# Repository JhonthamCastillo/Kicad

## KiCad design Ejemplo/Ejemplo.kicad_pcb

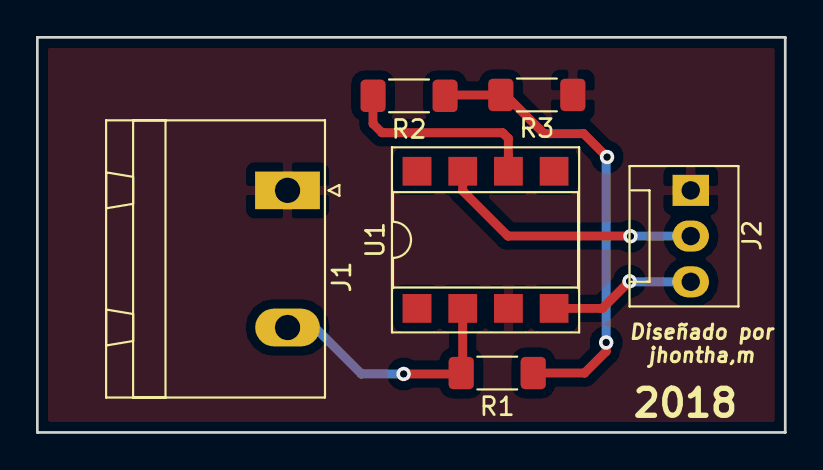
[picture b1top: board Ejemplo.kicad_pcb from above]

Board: 2 copper layers, 41.6 x 21.9 mm, 6 parts (0 on the bottom side), 6 nets.

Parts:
J1: Conn_01x02_Female; PhoenixContact_GMSTBA_2,5_2-G-7,62_1x02_P7.62mm_Horizontal
J2: Conn_01x03_Female; FanPinHeader_1x03_P2.54mm_Vertical
R1: 2k; R_1806_4516Metric
R2: 100; R_1806_4516Metric
R3: 1k; R_1806_4516Metric
U1: LM741; DIP-8_W7.62mm_SMDSocket_SmallPads

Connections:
+12V: J2.2, U1.7
-12V: J2.3, U1.4
GND: J1.1, J2.1, R3.1, U1.3
unnamed: J1.2, R1.2, U1.2
unnamed: R1.1, R2.1, R3.2
unnamed: R2.2, U1.6

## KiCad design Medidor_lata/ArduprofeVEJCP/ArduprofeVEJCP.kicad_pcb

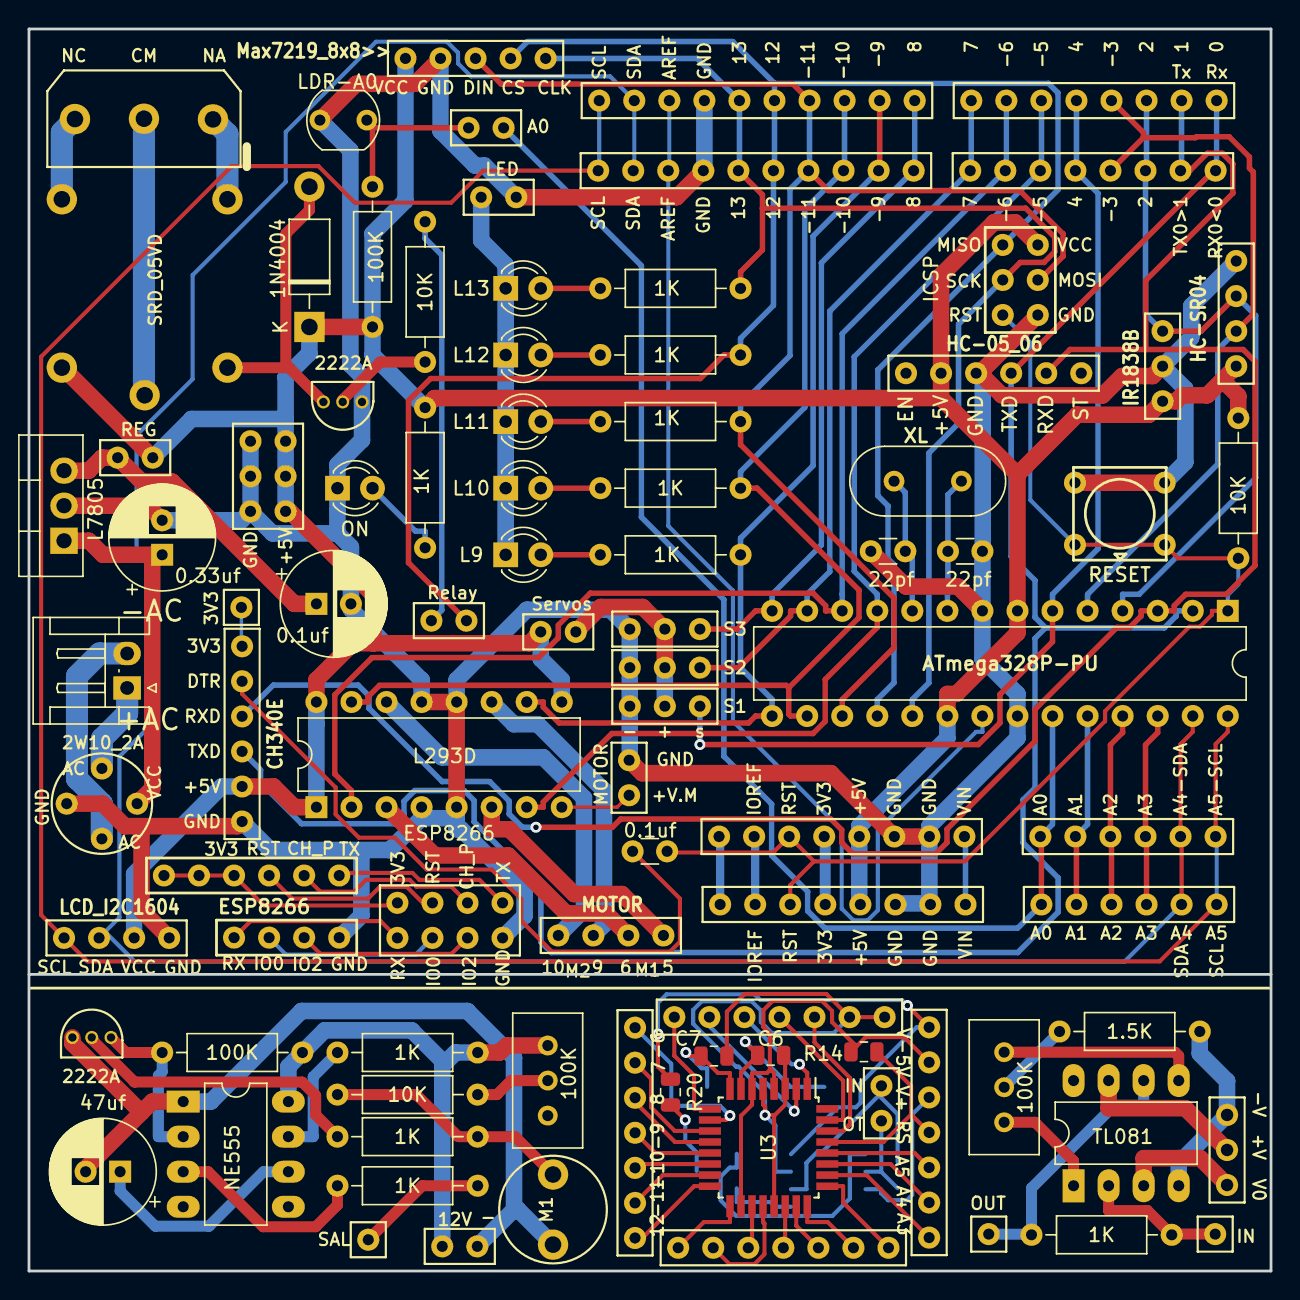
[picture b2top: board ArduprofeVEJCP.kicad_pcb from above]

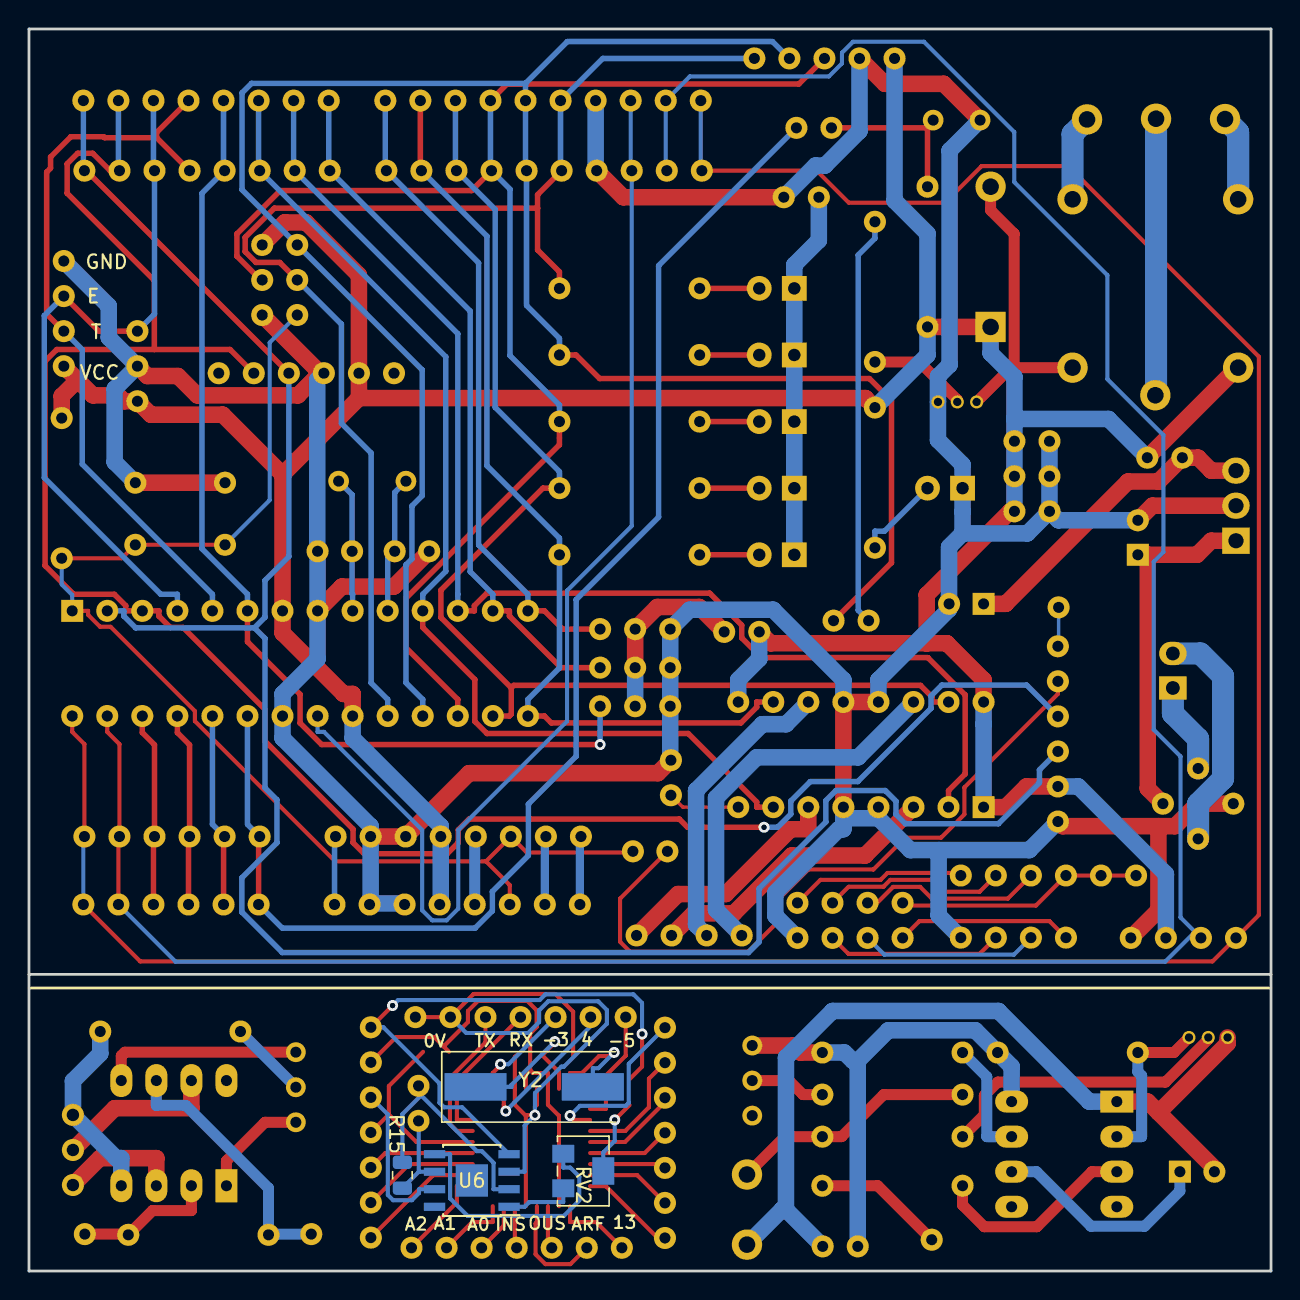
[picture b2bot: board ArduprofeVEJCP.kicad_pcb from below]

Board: 2 copper layers, 90.0 x 90.0 mm, 88 parts (4 on the bottom side), 115 nets.

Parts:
C1: 0.33uf; CP_Radial_D7.5mm_P2.50mm
C2: 0.1uf; CP_Radial_D7.5mm_P2.50mm
C3, C4: 22pf; C_Disc_D3.0mm_W1.6mm_P2.50mm
C5: 0.1uf; C_Disc_D3.0mm_W1.6mm_P2.50mm
C6, C7: 22p; C_0805_2012Metric
C8: 47uf; CP_Radial_D7.5mm_P2.50mm
CON1: SheldArduino; arduino_sheld
CONN1: ICSP
CONN2: S1; arduino_pin_servo
CONN3: S2; arduino_pin_servo
CONN4: ArduinoSheldExt; arduino_sheld_ext
CONN5: S3; arduino_pin_servo
CONN6: ESP8266; SocketESP8266
CONN7: Bornera_5.0_3P
CONN8: Max7219_8x8>>; Max7219_8x8
CONN9: MOTOR; L293D
D1: 1N4004; D_DO-41_SOD81_P10.16mm_Horizontal
D2: ON; LED_D3.0mm
D3: L9; LED_D3.0mm
D4: L10; LED_D3.0mm
D5: L11; LED_D3.0mm
D6: L12; LED_D3.0mm
D7: L13; LED_D3.0mm
J1: Conn_01x02_Female; POWER
J2: 3V3; arduino_pin_socket_1
J3: Conn_01x02_Female; JST_EH_S02B-EH_1x02_P2.50mm_Horizontal
J4: 12V; arduino_pin_socket_2
J5: IN; arduino_pin_socket_1
J6: OUT; arduino_pin_socket_1
J7: SAL; arduino_pin_socket_1
J8: Conn_01x03_Female; arduino_pin_socket_3
J9: ANALOG; arduino_pin_socket_7
J10, J11: DIGITAL; arduino_pin_socket_7
J12: Alimentacion; arduino_pin_socket_7
J13: Conn_01x02_Female; arduino_pin_socket_2
JP1: Relay; Jum2.54mm
JP2: A0; Jum2.54mm
JP3: MOTOR; Jum2.54mm
JP4: Servos; Jum2.54mm
JP5: LED; Jum2.54mm
JP6: REG; Jum2.54mm
LCD1: LCD_I2C1604; LCD_I2C_1604
M1: MIC
MOD1: ESP8266; WIFI_ESP8266
MOD2: HC-SR04
MOD3: HC-05_06
MOD4: CH340E; arduino_usb_ttl
Q1, Q2: 2222A; TRANSISTOR_TO_92ME
R1, R2, R11: 10K; R_Axial_DIN0207_L6.3mm_D2.5mm_P10.16mm_Horizontal
R3, R13: 100K; R_Axial_DIN0207_L6.3mm_D2.5mm_P10.16mm_Horizontal
R4, R6, R7, R8, R9, R10, R12, R16, R18, R19: 1K; R_Axial_DIN0207_L6.3mm_D2.5mm_P10.16mm_Horizontal
R5: LDR-A0; R_LDR_5.1x4.3mm_P3.4mm_Vertical
R14, R15: 1K; R_0805_2012Metric
R17: 1.5K; R_Axial_DIN0207_L6.3mm_D2.5mm_P10.16mm_Horizontal
R20: 1.5K; R_0805_2012Metric
RV1, RV3: 100K; Potentiometer_Bourns_3296W_Vertical
RV2: R_POT; Potentiometer_Bourns_3224W_Vertical
Relay1: SRD_05VD; SRD_05VDC_SL_C_5_V_DC_10A
SEN1: IR1838B; VS1838B
Sw1: RESET; Pulsador
U1: ATmega328P-PU; DIP-28_W7.62mm
U2: L7805; TO-220-3_Vertical
U3: ATmega328-AU; TQFP-32_7x7mm_P0.8mm
U4: L293D; DIP-16_W7.62mm
U5: 2W10_2A; 2W005_thru_2W10
U6: TL081; SOIC-8-1EP_3.9x4.9mm_P1.27mm_EP2.35x2.35mm
U7: NE555; DIP-8_W7.62mm_LongPads
U8: TL081; DIP-8_W7.62mm_LongPads
Y1: XL; Crystal_HC49-U_Vertical
Y2: XL; Crystal_SMD_HC49-SD

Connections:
3V3: CONN6.4, MOD1.4
4: J12.2, U3.2
7: J11.2, U3.11
8: J11.3, U3.12
12: J11.7, U3.16
13: J10.1, U3.17
+3V3: CON1.4, CONN4.4
+5V: CON1.5, CONN1.2, CONN4.5, CONN8.5, D1.1, J1.1, JP4.1, JP6.2, LCD1.2, MOD2.4, MOD3.2, MOD4.2, R2.2, R3.2, R4.1, Relay1.3, SEN1.3, U1.7, U1.20, U4.1, U4.9, U4.16
+30V: J3.1, U5.1
+S: CONN2.2, CONN3.2, CONN5.2, JP4.2
-3: J12.3, U3.1
-5: J12.1, U3.9
-6: J11.1, U3.10
-9: J11.4, U3.13
-10: J11.5, U3.14
-11: J11.6, U3.15
-30V: J3.2, U5.3
/C3: C3.2, U1.9, Y1.1
/C4: C4.1, U1.10, Y1.2
/C8: C8.1, U7.6
/INA: J5.1, R16.1, U8.2
/J412V: J4.2, R13.1, R18.2, RV1.3, U7.8
/L9: D3.2, R6.1
/L10: D4.2, R7.1
/L11: D5.2, R8.1
/L12: D6.2, R9.1
/L13: D7.2, R10.1
/LDR: JP2.1, R3.1, R5.2
/LED: D3.1, D4.1, D5.1, D6.1, D7.1, JP5.1
/LON: D2.2, R4.2
/M15: CONN9.1, U4.6
/M16: CONN9.2, U4.3
/M29: CONN9.3, U4.11
/M210: CONN9.4, U4.14
/M+: M1.2, R11.1, R12.2
/Micro328U/PV: R20.1, RV2.2
/OF1: RV3.3, U8.1
/OF2: RV3.1, U8.5
/OUTA: J6.1, R16.2, U8.6
/Q2B: Q2.2, R12.1
/Q2E: Q2.3, R13.2, U7.2
/QB: Q1.2, R1.1
/QE: D1.2, Q1.3, Relay1.1
/R18: R18.1, U7.7
/RL: JP1.1, R1.2
/RNA: CONN7.1, Relay1.5
/RNC: CONN7.3, Relay1.4
/RPT: R17.1, RV3.2
/RV1: R11.2, RV1.2
/SAL: J7.1, R19.1
/SSAL: R19.2, U7.3
AD6: J10.3, U3.19
AD7: J10.4, U3.22
AIN0: CON1.9, CONN4.9, JP2.2, U1.23
AIN1: CON1.10, CONN4.10, U1.24
AIN2: CON1.11, CONN4.11, U1.25
AIN3: CON1.12, CONN4.12, U1.26
AN0: J10.5, U3.23
AN1: J10.6, U3.24
AN2: J10.7, U3.25
AN3: J9.7, U3.26
AN4: J9.6, U3.27
AN5: J9.5, U3.28
AREF: CON1.30, CONN4.30, U1.21
ARF: J10.2, U3.20
C: CONN7.2, Relay1.2
CH: CONN6.2, MOD1.2
D2: CON1.17, CONN4.17, MOD2.2, SEN1.1, U1.4
D4: CON1.19, CONN2.3, CONN4.19, U1.6
D7: CON1.22, CONN3.3, CONN4.22, U1.13
D8: CON1.23, CONN4.23, CONN5.3, U1.14
D12: CON1.27, CONN1.1, CONN4.27, CONN8.2, JP1.2, R9.2, U1.18
D13: CON1.28, CONN1.3, CONN4.28, CONN8.1, R10.2, U1.19
DT: C5.1, MOD4.5
GND: C1.2, C2.2, C3.1, C4.2, CON1.6, CON1.7, CON1.29, CONN1.6, CONN2.1, CONN3.1, CONN4.6, CONN4.7, CONN4.29, CONN5.1, CONN6.8, CONN8.4, D2.1, J1.2, JP3.2, JP5.2, LCD1.1, MOD1.8, MOD2.1, MOD3.3, MOD4.1, Q1.1, R5.1, SEN1.2, Sw1.2, U1.8, U1.22, U2.2, U4.4, U4.5, U4.12, U4.13, U5.4
GND1: J8.1, U8.3
GND2: C8.2, J4.1, M1.1, Q2.1, U7.1
GND3: C6.1, C7.1, J12.6, J12.7, U3.3, U3.5, U3.21, U6.3
INS: J13.2, R15.2, U6.2
IO0: CONN6.6, MOD1.6
IO2: CONN6.7, MOD1.7
IOREF: CON1.2, CONN4.2
NC: CON1.1, CONN4.1
unnamed: J2.1, MOD4.6
unnamed: JP3.1, U4.8
OF1: RV2.3, U6.1
OF2: RV2.1, U6.5
OUTS: J13.1, R15.1, U6.6
PR: C1.1, U2.1, U5.2
PWM3: CON1.18, CONN4.18, MOD2.3, U1.5
PWM5: CON1.20, CONN4.20, U1.11, U4.7
PWM6: CON1.21, CONN4.21, U1.12, U4.2
PWM9: CON1.24, CONN4.24, R6.2, U1.15, U4.10
PWM10: CON1.25, CONN4.25, R7.2, U1.16, U4.15
PWM11: CON1.26, CONN1.4, CONN4.26, CONN8.3, R8.2, U1.17
RS: CONN6.3, MOD1.3
RS1: J9.4, R14.2, U3.29
RST: C5.2, CON1.3, CONN1.5, CONN4.3, R2.1, Sw1.1, U1.1
RX: CON1.15, CONN4.15, MOD3.4, MOD4.3, U1.2
RX1: CONN6.5, MOD1.5
RX2: J12.4, U3.31
Reg: C2.1, JP6.1, U2.3
SCL: CON1.14, CON1.32, CONN4.14, CONN4.32, LCD1.4, U1.28
SDA: CON1.13, CON1.31, CONN4.13, CONN4.31, LCD1.3, U1.27
TX: CON1.16, CONN4.16, MOD3.5, MOD4.4, U1.3
TX1: CONN6.1, MOD1.1
TX2: J12.5, U3.30
V+: J9.3, U6.7
V-: J9.1, R20.2, U6.4
VC+: J9.2, R14.1, U3.4, U3.6, U3.18
VCC+: J8.2, U8.7
VCC-: J8.3, R17.2, U8.4
VIN: CON1.8, CONN4.8
XT1: C6.2, U3.7, Y2.1
XT2: C7.2, U3.8, Y2.2

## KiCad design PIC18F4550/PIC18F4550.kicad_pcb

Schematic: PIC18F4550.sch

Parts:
D1, D2, D3, D4, D5, D6, D7, D8: LED; LED_0402_1005Metric
R1, R2, R3, R4, R5, R6, R7, R8: R; R_0603_1608Metric
U1: PIC18F4550-IP; DIP-40_W15.24mm

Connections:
+5V: U1.11 (VDD), U1.32 (VDD)
GND: R1.2, R2.2, R3.2, R4.2, R5.2, R6.2, R7.2, R8.2, U1.12 (VSS), U1.31 (VSS)
unnamed: D1.1, R1.1
unnamed: D1.2, U1.33 (RB0/AN12/INT0/FLT0/SDI/SDA)
unnamed: D2.1, R2.1
unnamed: D2.2, U1.34 (RB1/AN10/INT1/SCK/SCL)
unnamed: D3.1, R3.1
unnamed: D3.2, U1.35 (RB2/AN8/INT2/VMO)
unnamed: D4.1, R4.1
unnamed: D4.2, U1.36 (RB3/AN9/CCP2/VPO)
unnamed: D5.1, R5.1
unnamed: D5.2, U1.37 (RB4/AN11/KBI0/CSSPP)
unnamed: D6.1, R6.1
unnamed: D6.2, U1.38 (RB5/KBI1/PGM)
unnamed: D7.1, R7.1
unnamed: D7.2, U1.39 (RB6/KBI2/PGC)
unnamed: D8.1, R8.1
unnamed: D8.2, U1.40 (RB7/KBI3/PGD)

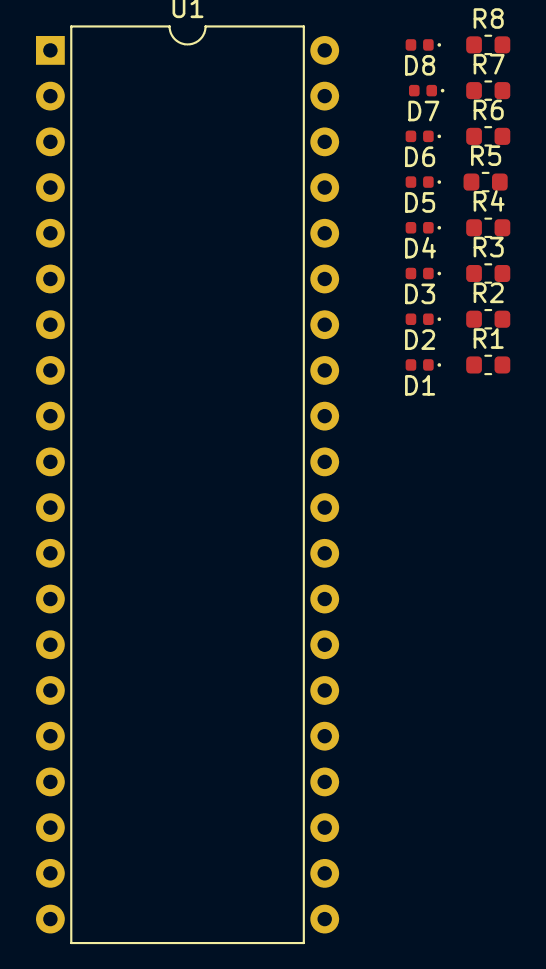
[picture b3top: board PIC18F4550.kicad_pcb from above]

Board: 2 copper layers, 17 parts (0 on the bottom side), 18 nets, no tracks yet.

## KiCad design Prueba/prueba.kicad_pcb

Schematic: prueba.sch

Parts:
C1, C2: C; C_Disc_D3.4mm_W2.1mm_P2.50mm
R1, R2: R; R_Axial_DIN0204_L3.6mm_D1.6mm_P5.08mm_Horizontal
U1: LM555; DIP-8_W7.62mm

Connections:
GND: C1.2, C2.2, U1.1 (GND)
unnamed: C1.1, U1.5 (CV)
unnamed: C2.1, R2.2, U1.2 (TR), U1.6 (THR)
unnamed: R1.2, R2.1, U1.7 (DIS)
VCC: R1.1, U1.4 (R), U1.8 (VCC)

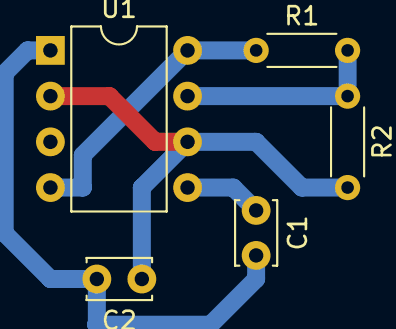
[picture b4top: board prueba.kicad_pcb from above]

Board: 2 copper layers, 5 parts (0 on the bottom side), 5 nets.

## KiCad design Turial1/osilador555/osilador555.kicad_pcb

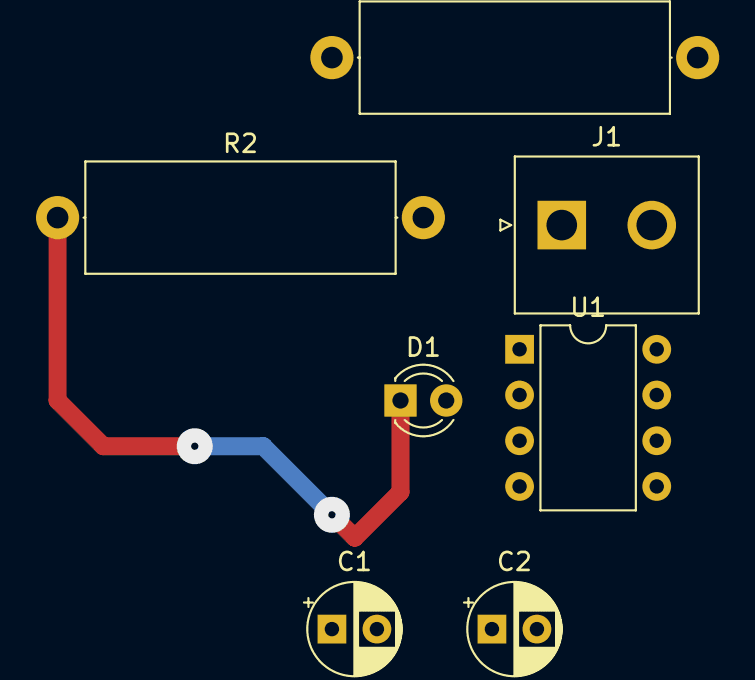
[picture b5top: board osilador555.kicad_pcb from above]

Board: 4 copper layers, 7 parts (0 on the bottom side), 6 nets.

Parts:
C1, C2: CP; CP_Radial_D5.0mm_P2.50mm
D1: LED; LED_D3.0mm
J1: Conn_01x02_Female; JST_NV_B02P-NV_1x02_P5.00mm_Vertical
R1, R2: R; R_Axial_DIN0617_L17.0mm_D6.0mm_P20.32mm_Horizontal
U1: LM555; DIP-8_W7.62mm

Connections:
GND: C1.2, C2.2, J1.1, R2.2
unnamed: C1.1, U1.5
unnamed: C2.1, R1.2, U1.6, U1.7
unnamed: D1.1, R2.1
unnamed: D1.2, U1.3
VCC: J1.2, R1.1, U1.2, U1.4
